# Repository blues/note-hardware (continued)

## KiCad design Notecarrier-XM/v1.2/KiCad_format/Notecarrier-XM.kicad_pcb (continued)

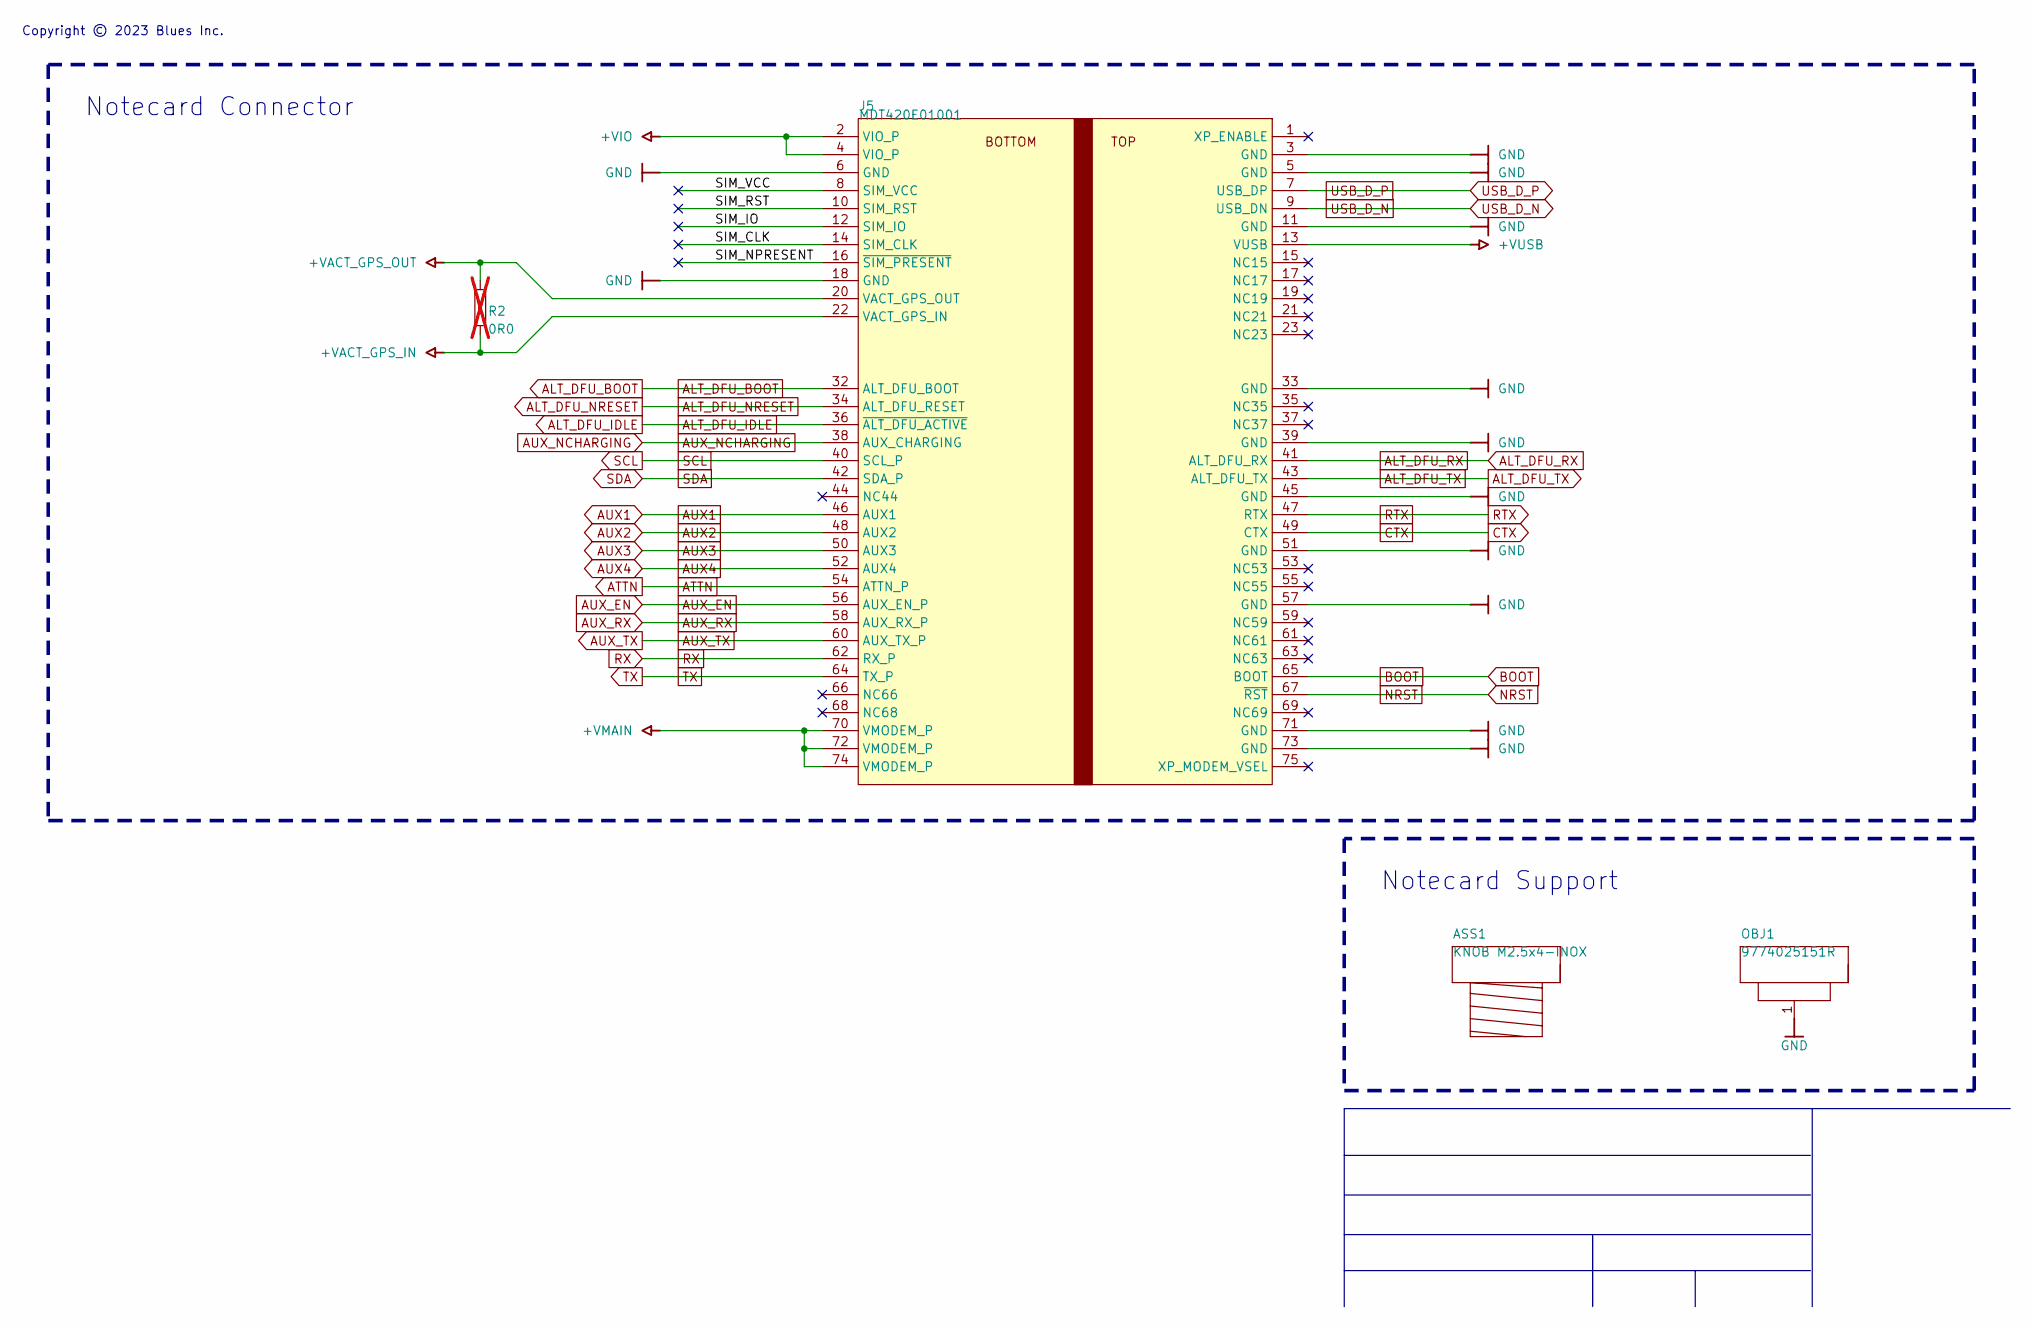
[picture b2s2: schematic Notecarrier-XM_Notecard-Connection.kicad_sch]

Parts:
ASS1: KNOB M2.5x4-INOX; MANUFACTURER PART NUMBER M2.5X4/D7985-A2
J5: MDT420E01001; J-75-0050-MOS-M2; MANUFACTURER PART NUMBER MDT420E03001
OBJ1: 9774025151R; DIST-WASMSIM0250; MANUFACTURER PART NUMBER 9774025151R
R2: 0R0; R-0603; MANUFACTURER PART NUMBER N/A; not fitted

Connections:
+VACT_GPS_IN: J5.22 (VACT_GPS_IN), R2.1; also elsewhere on the board
+VACT_GPS_OUT: J5.20 (VACT_GPS_OUT), R2.2; also elsewhere on the board
+VIO: J5.2 (VIO_P), J5.4 (VIO_P); also elsewhere on the board
+VMAIN: J5.70 (VMODEM_P), J5.72 (VMODEM_P), J5.74 (VMODEM_P); also elsewhere on the board
+VUSB: J5.13 (VUSB); also elsewhere on the board
/Notecard Connection/SIM_CLK: J5.14 (SIM_CLK)
/Notecard Connection/SIM_IO: J5.12 (SIM_IO)
/Notecard Connection/SIM_NPRESENT: J5.16 (~SIM_PRESENT)
/Notecard Connection/SIM_RST: J5.10 (SIM_RST)
/Notecard Connection/SIM_VCC: J5.8 (SIM_VCC)
ALT_DFU_BOOT: J5.32 (ALT_DFU_BOOT); also elsewhere on the board
ALT_DFU_IDLE: J5.36 (~ALT_DFU_ACTIVE); also elsewhere on the board
ALT_DFU_NRESET: J5.34 (ALT_DFU_RESET); also elsewhere on the board
ALT_DFU_RX: J5.41 (ALT_DFU_RX); also elsewhere on the board
ALT_DFU_TX: J5.43 (ALT_DFU_TX); also elsewhere on the board
ATTN: J5.54 (ATTN_P); also elsewhere on the board
AUX1: J5.46 (AUX1); also elsewhere on the board
AUX2: J5.48 (AUX2); also elsewhere on the board
AUX3: J5.50 (AUX3); also elsewhere on the board
AUX4: J5.52 (AUX4); also elsewhere on the board
AUX_EN: J5.56 (AUX_EN_P); also elsewhere on the board
AUX_NCHARGING: J5.38 (AUX_CHARGING); also elsewhere on the board
AUX_RX: J5.58 (AUX_RX_P); also elsewhere on the board
AUX_TX: J5.60 (AUX_TX_P); also elsewhere on the board
BOOT: J5.65 (BOOT); also elsewhere on the board
CTX: J5.49 (CTX); also elsewhere on the board
GND: J5.3 (GND), J5.5 (GND), J5.6 (GND), J5.11 (GND), J5.18 (GND), J5.33 (GND), J5.39 (GND), J5.45 (GND), J5.51 (GND), J5.57 (GND), J5.71 (GND), J5.73 (GND), OBJ1.1; also elsewhere on the board
NRST: J5.67 (~RST); also elsewhere on the board
RTX: J5.47 (RTX); also elsewhere on the board
RX: J5.62 (RX_P); also elsewhere on the board
SCL: J5.40 (SCL_P); also elsewhere on the board
SDA: J5.42 (SDA_P); also elsewhere on the board
TX: J5.64 (TX_P); also elsewhere on the board
USB_D_N: J5.9 (USB_DN); also elsewhere on the board
USB_D_P: J5.7 (USB_DP); also elsewhere on the board

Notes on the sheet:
Copyright © 2023 Blues Inc.
Notecard Connector
Notecard Support

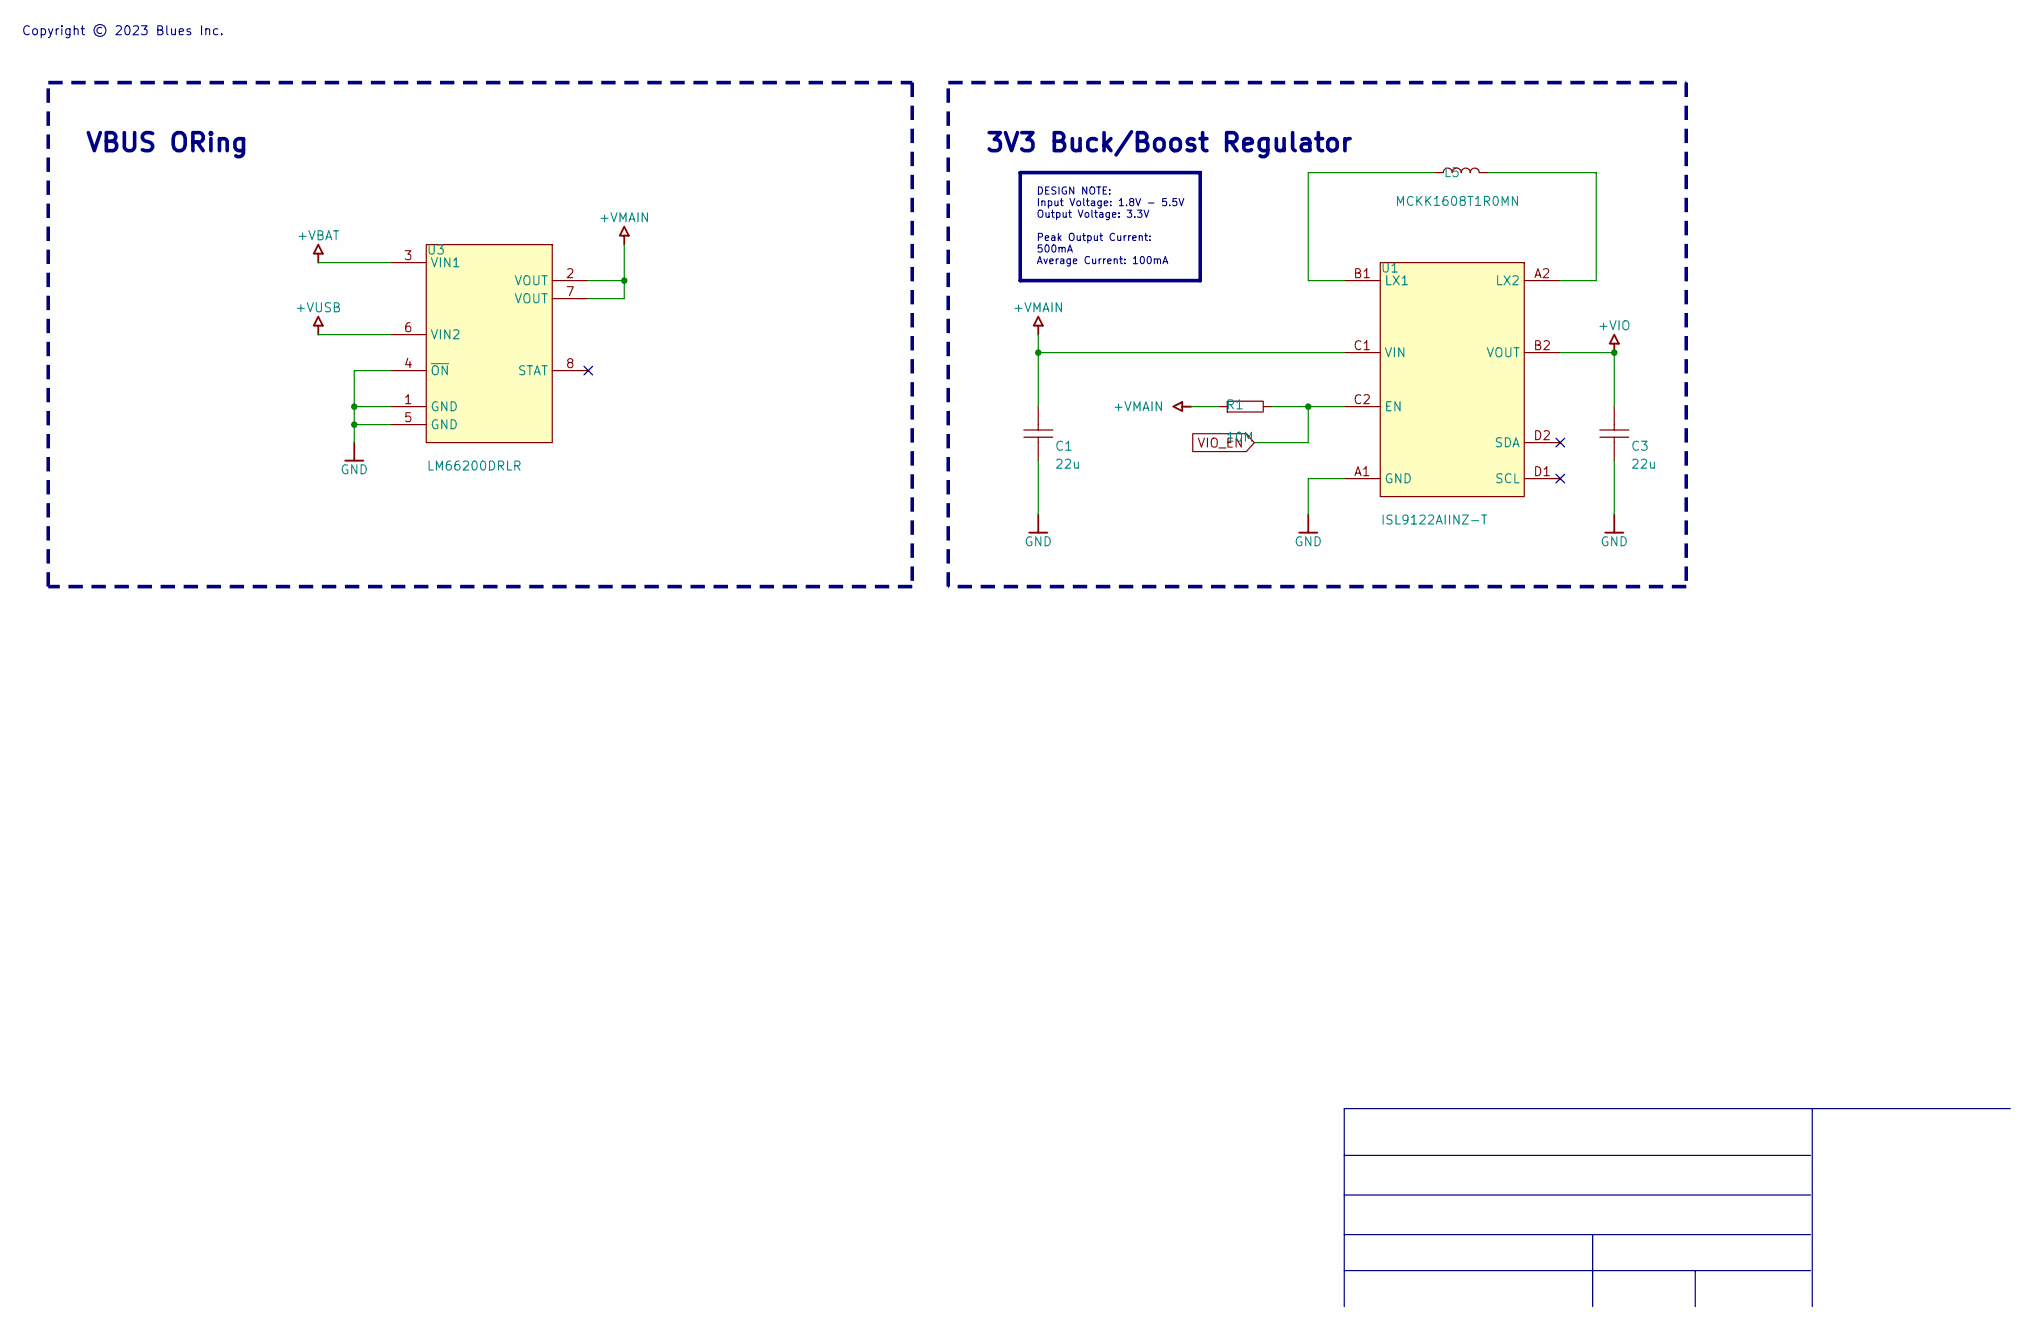
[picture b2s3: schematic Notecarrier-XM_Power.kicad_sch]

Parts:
C1, C3: 22u; C-0805; MANUFACTURER PART NUMBER N/A
L5: MCKK1608T1R0MN; L-0603; MANUFACTURER PART NUMBER MCKK1608T1R0MN
R1: 10M; R-0402; MANUFACTURER PART NUMBER N/A
U1: ISL9122AIINZ-T; BGA8N40P2X4_180x100x50; MANUFACTURER PART NUMBER ISL9122AIINZ-T
U3: LM66200DRLR; SOT-583; MANUFACTURER PART NUMBER LM66200DRLR

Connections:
+VBAT: U3.3 (VIN1); also elsewhere on the board
+VIO: C3.2, U1.B2 (VOUT); also elsewhere on the board
+VMAIN: C1.2, R1.1, U1.C1 (VIN), U3.2 (VOUT), U3.7 (VOUT); also elsewhere on the board
+VUSB: U3.6 (VIN2); also elsewhere on the board
GND: C1.1, C3.1, U1.A1 (GND), U3.1 (GND), U3.4 (~ON), U3.5 (GND); also elsewhere on the board
unnamed: L5.1, U1.B1 (LX1)
unnamed: L5.2, U1.A2 (LX2)
VIO_EN: R1.2, U1.C2 (EN); also elsewhere on the board

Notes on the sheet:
3V3 Buck/Boost Regulator
Copyright © 2023 Blues Inc.
VBUS ORing
DESIGN NOTE: Input Voltage: 1.8V - 5.5V Output Voltage: 3.3V Peak Output Current: 500mA Average Current: 100mA

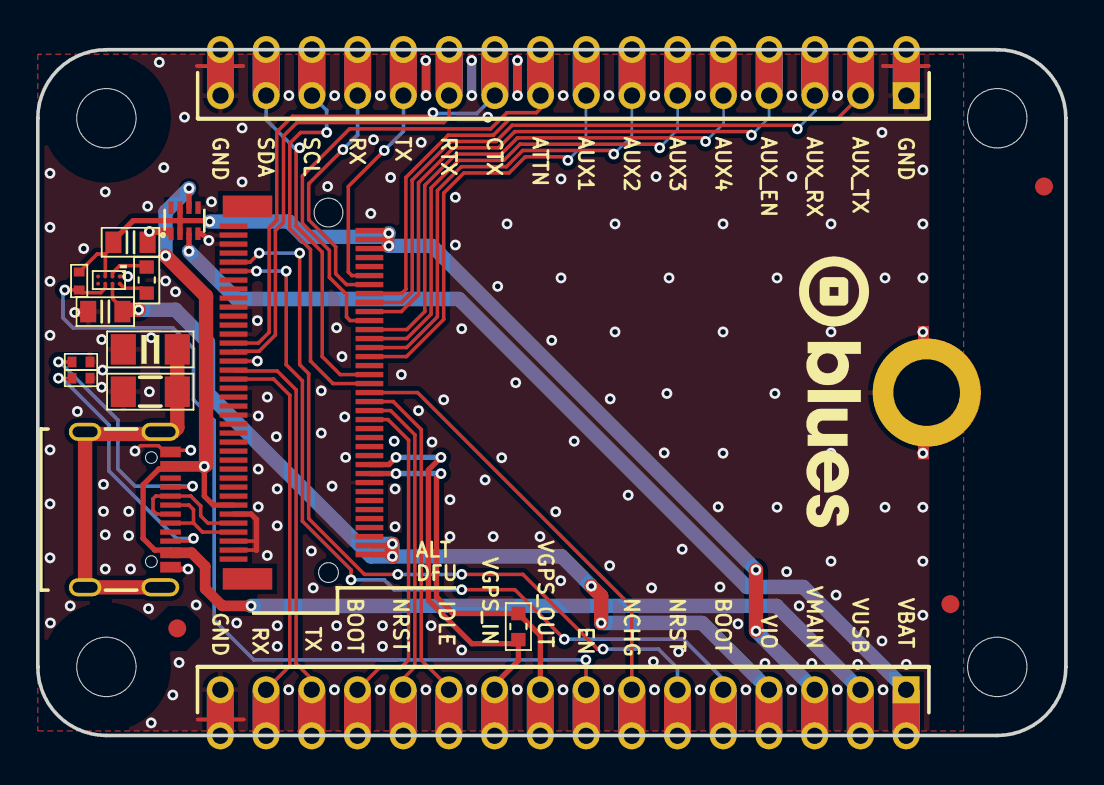
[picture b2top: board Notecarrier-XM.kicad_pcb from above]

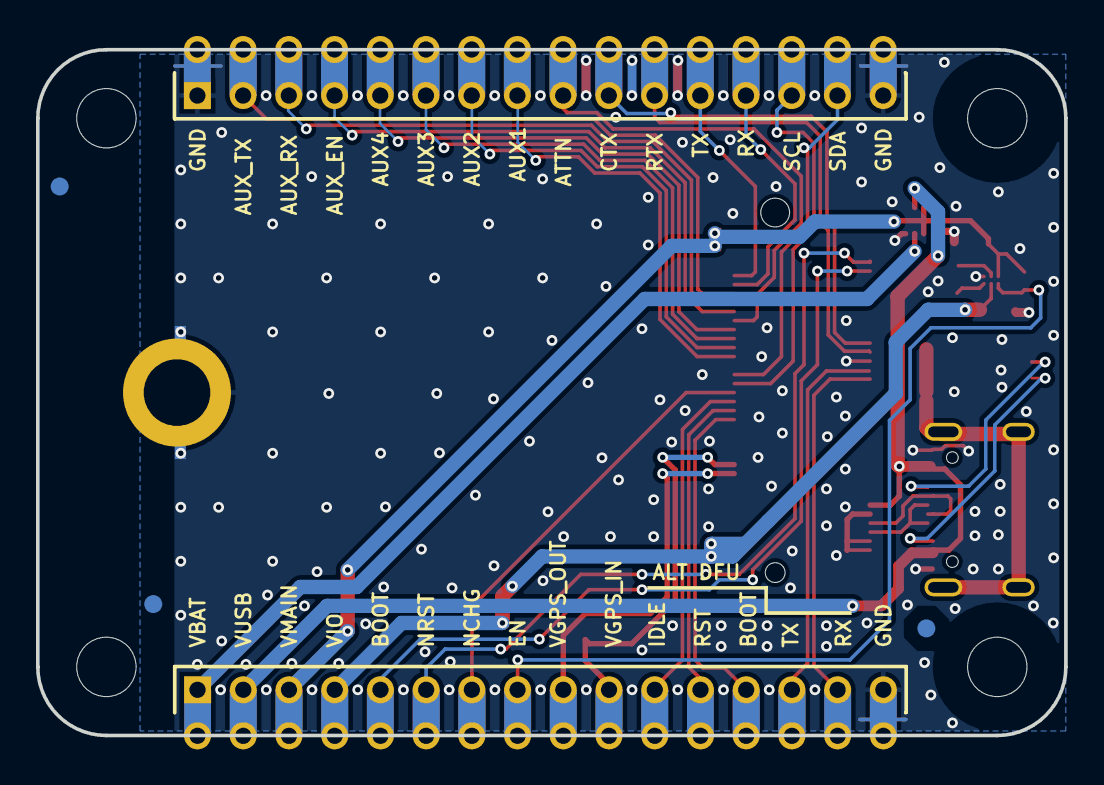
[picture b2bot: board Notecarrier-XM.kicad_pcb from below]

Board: 2 copper layers, 57.1 x 38.1 mm, 22 parts (3 on the bottom side), 37 nets.

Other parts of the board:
FD1, FD2, FD3, FD5, FD6, FD7: Fiducial mark; Fiducial mark 1mm

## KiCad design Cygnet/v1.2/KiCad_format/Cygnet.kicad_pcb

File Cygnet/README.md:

# Cygnet

STM32L433CC in Adafruit Feather form factor

  - Schematics
  - Bills of material
  - PCB layouts and Gerber files
  - Dimensioned drawings
  - KiCad design files ([v1.2/KiCad_format](v1.2/KiCad_format), converted from the original sources and validated against the shipped fabrication outputs)

> **⚠️ One open discrepancy in the KiCad port.** Inner layer 1 (`In1_Cu`) carries
> roughly fifty annular rings that the shipped Gerbers do not, so its fabrication
> equivalence on that layer is **not proven** and the gerber gate fails. Every
> other layer matches, and the schematic, netlist and BOM are exact. See
> [the porting notes](v1.2/KiCad_format/documentation/Porting-Notes.md) before
> using these files to manufacture.

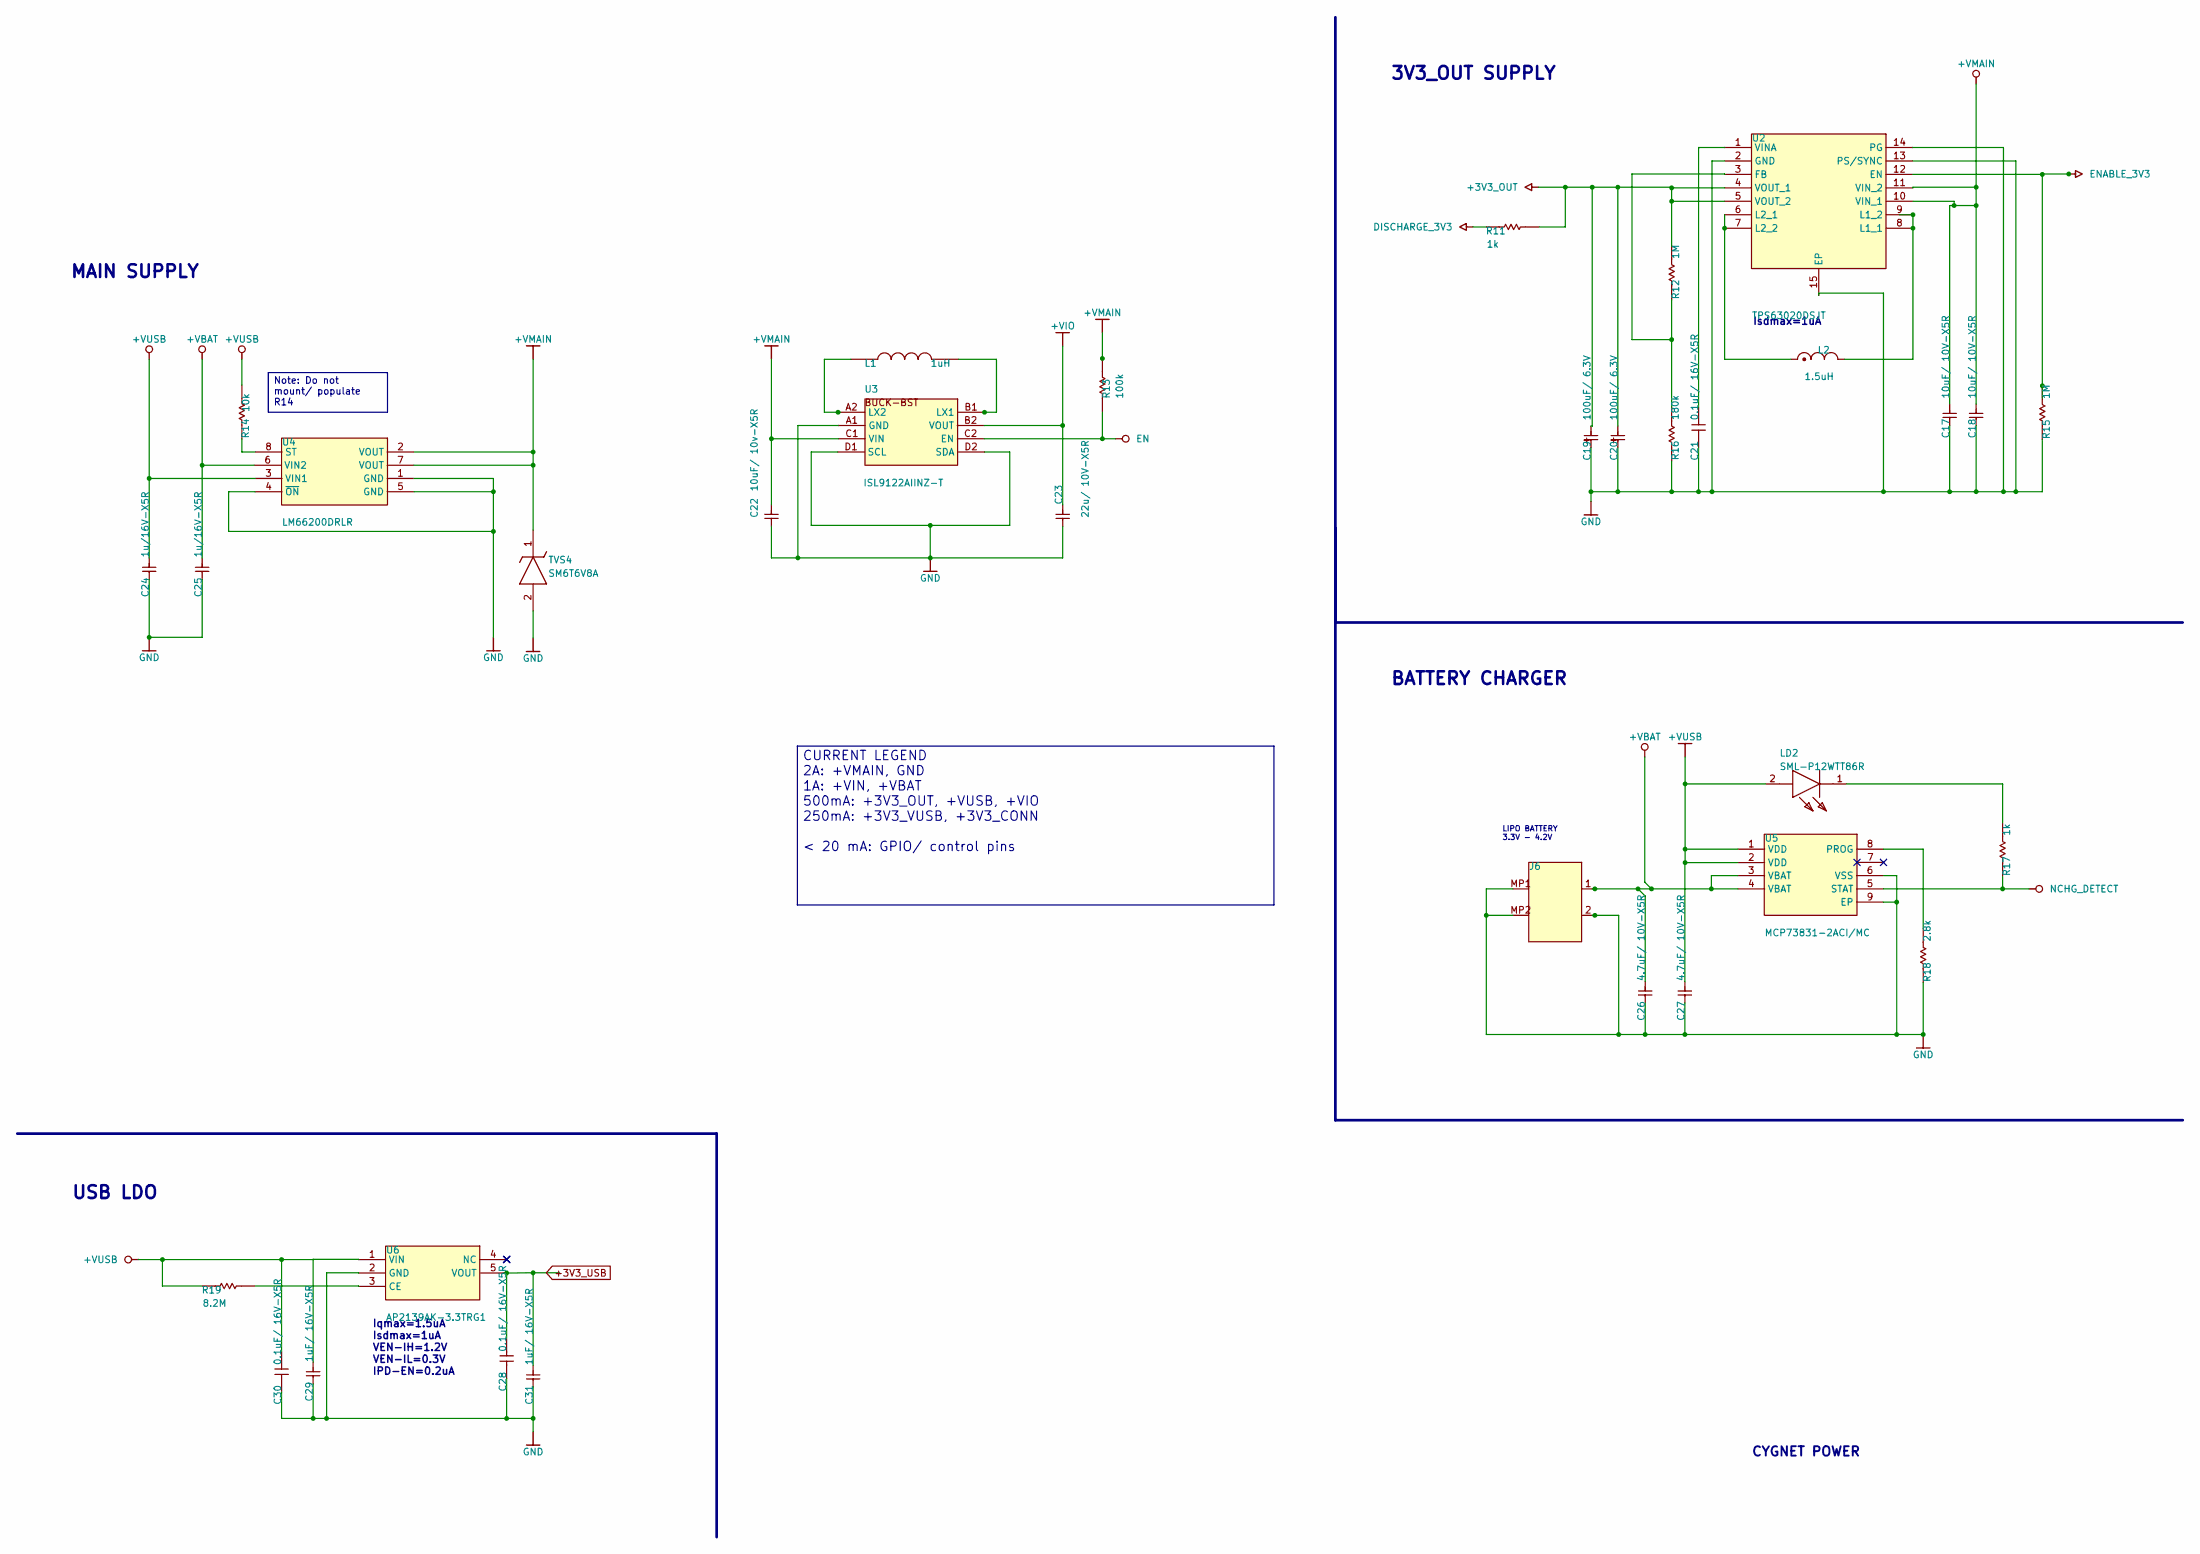
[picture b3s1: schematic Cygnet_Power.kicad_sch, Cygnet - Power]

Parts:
C17, C18: 10uF/ 10V-X5R; FP-GRM18-0_15-IPC_A; MPN GRM188R61A106KE69D
C19, C20: 100uF/ 6.3V; F930J107KAABE1-Footprint-1; MPN F930J107KAABE1
C21, C28, C30: 0.1uF/ 16V-X5R; GRM033R61C104KE84J-Footprint-1; MPN GRM033R61C104KE84J
C22: 10uF/ 10v-X5R; FP-GRM18-0_15-IPC_A; MPN GRM188R61A106KE69D
C23: 22u/ 10V-X5R; FP-GRM18-0_15-IPC_A; MPN GRM188R61A106KE69D
C24, C25: 1u/16V-X5R; C0402B105K016T-Footprint-1; MPN C0402B105K016T
C26, C27: 4.7uF/ 10V-X5R; FP-CL10-IPC_B; MPN CL10A475KP8NNNC
C29, C31: 1uF/ 16V-X5R; C0402B105K016T-Footprint-1; MPN C0402B105K016T
J6: 1769 - JST-PH 2-PIN SMT; 1769 - JST-PH 2-PIN SMT-Footprint-1
L1: 1uH; MCKK1608T1R0MN-Footprint-1; MPN MCKK1608T1R0MN
L2: 1.5uH; FP-XFL4020-MFG; MPN XFL4020-152MEC
LD2: SML-P12WTT86R; SML-P12WTT86R-Footprint-1; MPN SML-P12WTT86R
R11: 1k; RESC1005X40X25ML05T05; TOLERANCE 1%; MPN RC0402FR-071KL
R12, R15: 1M; RESC0201(0603)_M; MPN RC0201FR-071ML
R13: 100k; RESC0201(0603)_M
R14: 10k; RESC0603X26X15NL03T05; MPN MC0201L6F1002SE
R16: 180k; MR02X1803FAL-Footprint-1; MPN MR02X1803FAL
R17: 1k; RESC0603X28X15ML05T05; MPN CRCW02011K00FNED
R18: 2.8k; RESC0603X28X15ML05T05; MPN CRCW02012K80FKED
R19: 8.2M; CRCW02018M20FNED-Footprint-1; MPN CRCW02018M20FNED
TVS4: SM6T6V8A; SM6T6V8A-Footprint-1; MPN SM6T6V8A
U2: TPS63020DSJT; FP-DSJ0014A-MFG; MPN TPS63020DSJT
U3: ISL9122AIINZ-T; ISL9122AIINZ-T-Footprint-1; MPN ISL9122AIINZ-T
U4: LM66200DRLR; LM66200DRLR-Footprint-2; MPN LM66200DRLR
U5: MCP73831-2ACI/MC; FP-C04-123-IPC_A; MPN MCP73831-2ACI/MC
U6: AP2139AK-3.3TRG1; AP2139AK-3.3TRG1-Footprint-1

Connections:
+3V3_OUT: C19.1, C20.1, R11.2, R12.2, U2.4 (VOUT_1), U2.5 (VOUT_2); also elsewhere on the board
+3V3_USB: C28.1, C31.1, U6.5 (VOUT); also elsewhere on the board
+VBAT: C25.1, C26.1, J6.1, U4.6 (VIN2), U5.3 (VBAT), U5.4 (VBAT); also elsewhere on the board
+VIO: C23.1, U3.B2 (VOUT); also elsewhere on the board
+VMAIN: C17.1, C18.1, C22.1, R13.2, TVS4.1 (K), U2.10 (VIN_1), U2.11 (VIN_2), U3.C1 (VIN), U4.2 (VOUT), U4.7 (VOUT); also elsewhere on the board
+VUSB: C24.1, C27.1, C29.1, C30.1, LD2.2 (A), R14.2, R19.1, U4.3 (VIN1), U5.1 (VDD), U5.2 (VDD), U6.1 (VIN); also elsewhere on the board
DISCHARGE_3V3: R11.1; also elsewhere on the board
EN: R13.1, U3.C2 (EN); also elsewhere on the board
ENABLE_3V3: R15.2, U2.12 (EN); also elsewhere on the board
GND: C17.2, C18.2, C19.2, C20.2, C21.2, C22.2, C23.2, C24.2, C25.2, C26.2, C27.2, C28.2, C29.2, C30.2, C31.2, J6.2, J6.MP1, J6.MP2, R15.1, R16.1, R18.1, TVS4.2 (A), U2.2 (GND), U2.13 (PS/SYNC), U2.14 (PG), U2.15 (EP), U3.A1 (GND), U3.D1 (SCL), U3.D2 (SDA), U4.1 (GND), U4.4 (~ON), U4.5 (GND), U5.6 (VSS), U5.9 (EP), U6.2 (GND); also elsewhere on the board
NCHG_DETECT: R17.1, U5.5 (STAT); also elsewhere on the board
unnamed: LD2.1 (K), R17.2
unnamed: R12.1, R16.2, U2.3 (FB)
unnamed: L2.2, U2.8 (L1_1), U2.9 (L1_2)
unnamed: L2.1, U2.6 (L2_1), U2.7 (L2_2)
unnamed: C21.1, U2.1 (VINA)
unnamed: L1.2, U3.B1 (LX1)
unnamed: L1.1, U3.A2 (LX2)
unnamed: R14.1, U4.8 (ST)
unnamed: R18.2, U5.8 (PROG)
unnamed: R19.2, U6.3 (CE)

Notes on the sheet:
MAIN SUPPLY
CYGNET POWER
BATTERY CHARGER
Isdmax=1uA
3V3_OUT SUPPLY
USB LDO
Iqmax=1.5uA Isdmax=1uA VEN-IH=1.2V VEN-IL=0.3V IPD-EN=0.2uA
LIPO BATTERY 3.3V - 4.2V
Note: Do not mount/ populate R14
CURRENT LEGEND 2A: +VMAIN, GND 1A: +VIN, +VBAT 500mA: +3V3_OUT, +VUSB, +VIO 250mA: +3V3_VUSB, +3V3_CONN < 20 mA: GPIO/ control pins

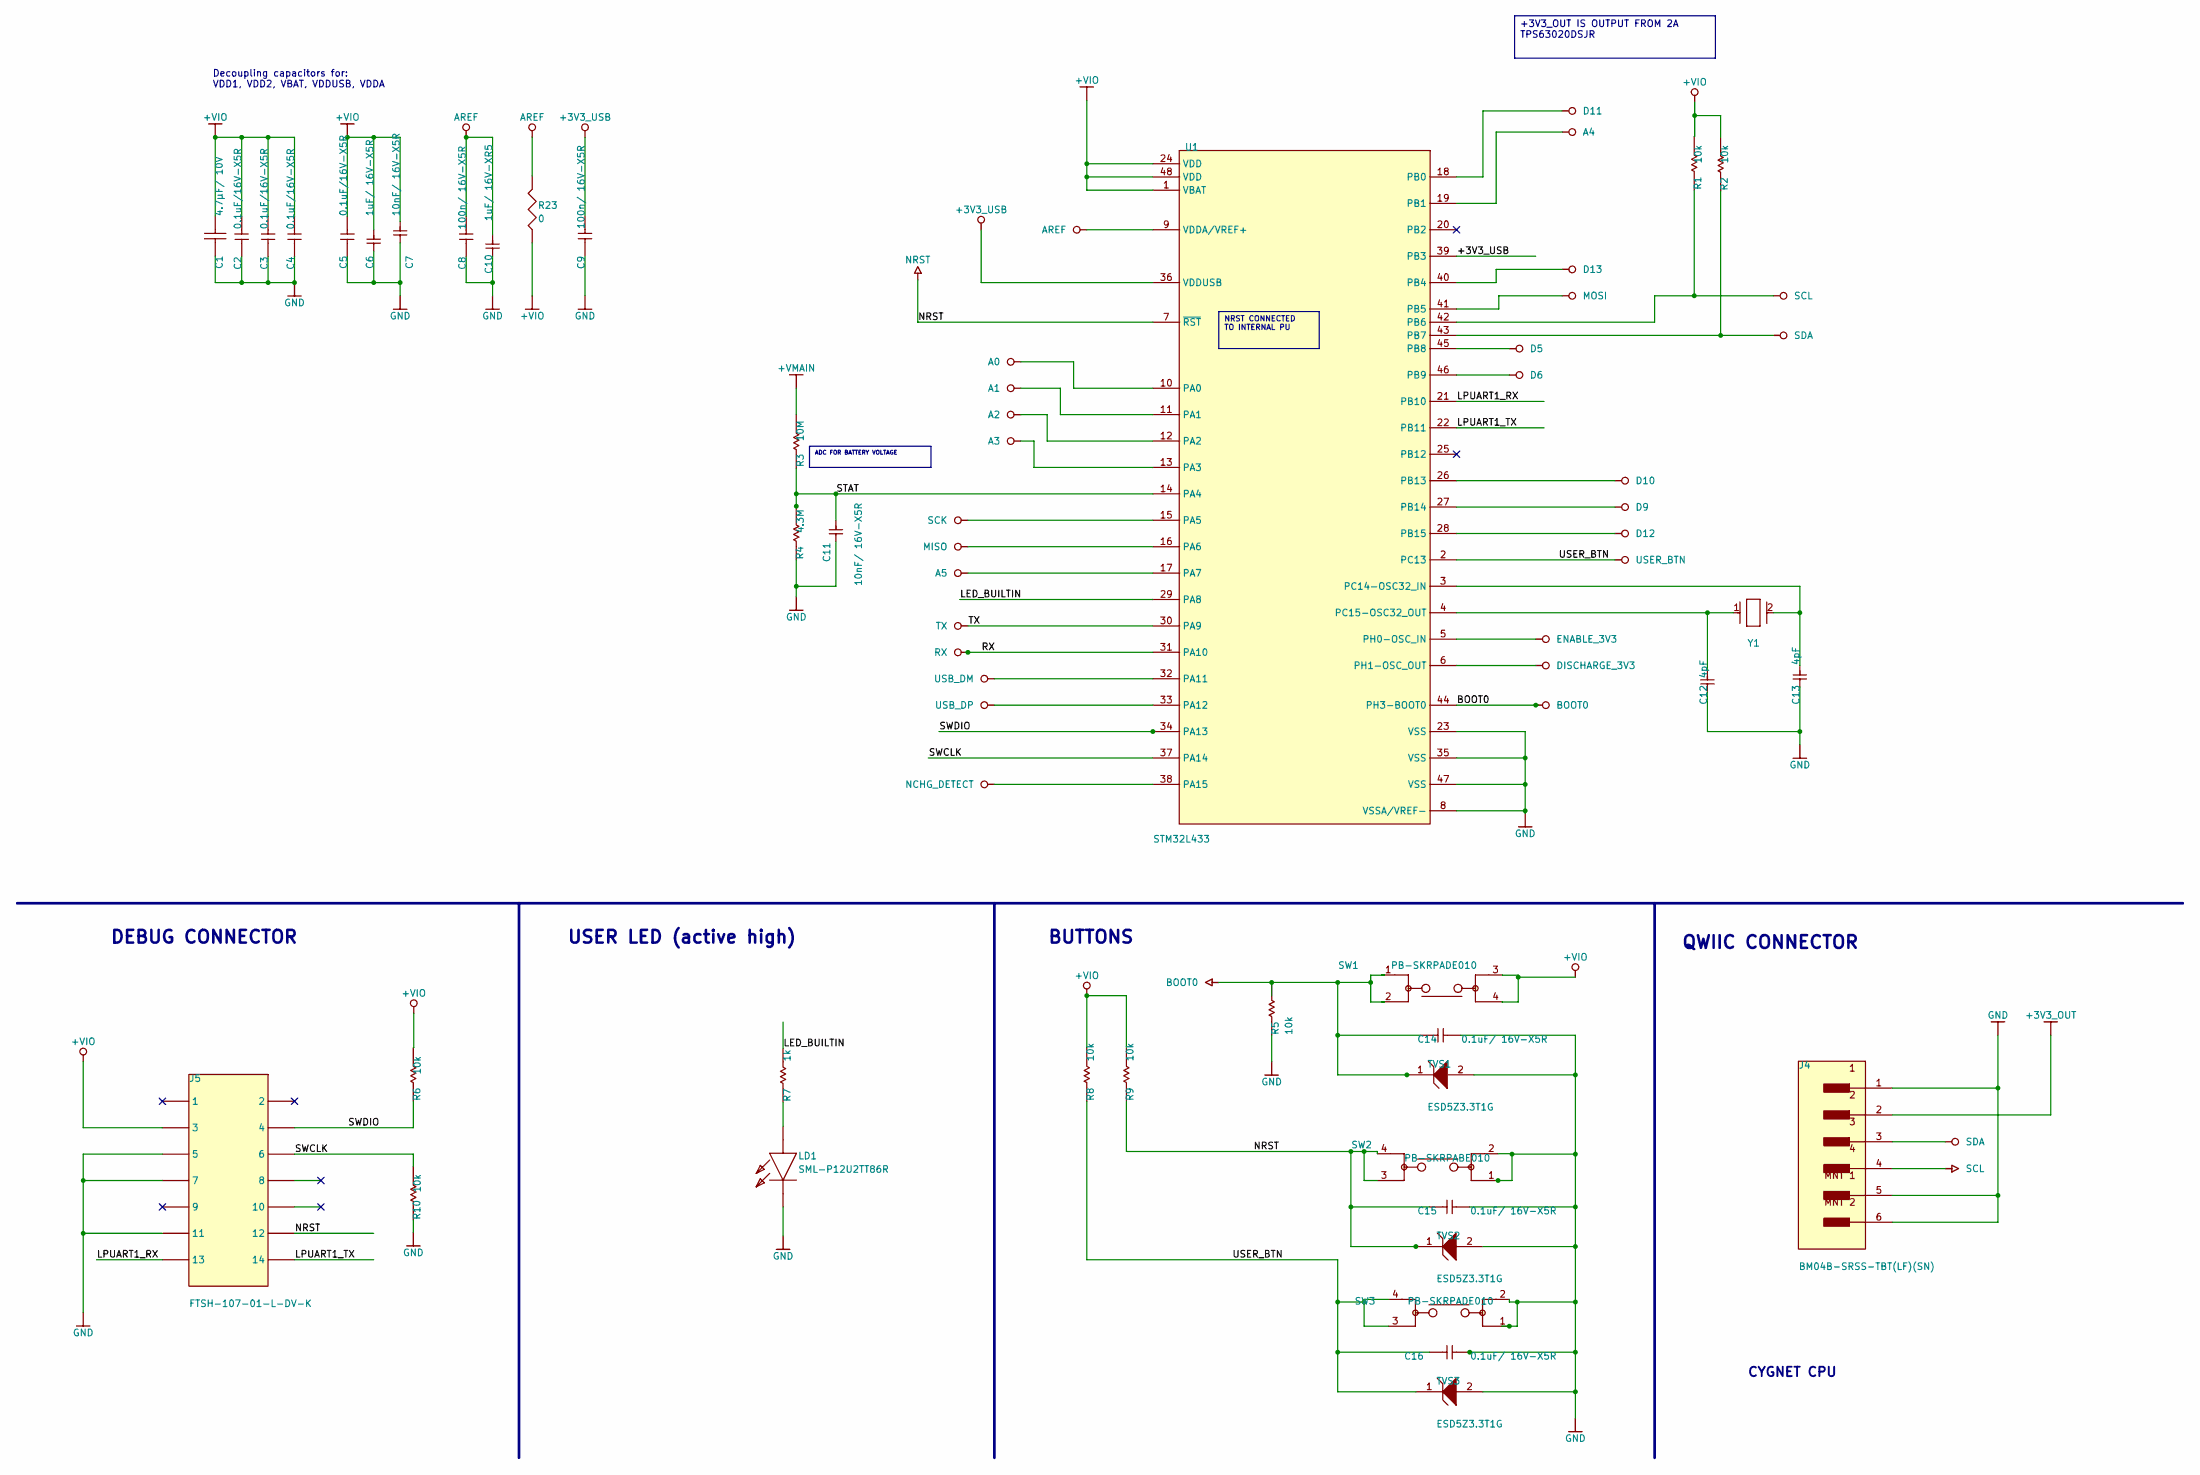
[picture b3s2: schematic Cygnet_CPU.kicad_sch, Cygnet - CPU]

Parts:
C1: 4.7µF/ 10V; CAPC0603(1608)100_L; TOLERANCE 10%; VOLTAGE RATING 10V; MPN C1608X5R1A475K/0.50
C2, C3, C4, C5: 0.1uF/16V-X5R; GRM033R61C104KE84J-Footprint-1; MPN GRM033R61C104KE84J
C6: 1uF/ 16V-X5R; C0402B105K016T-Footprint-1; MPN C0402B105K016T
C7, C11: 10nF/ 16V-X5R; FP-GRM033-0_03-MFG; MPN GRM033R61C103KA12D
C8, C9: 100n/ 16V-X5R; GRM033R61C104KE84J-Footprint-1; MPN GRM033R61C104KE84J
C10: 1uF/ 16V-XR5; C0402B105K016T-Footprint-1; MPN C0402B105K016T
C12, C13: 4pF; FP-GRM033-0_03-MFG; MPN GRM0335C1H4R0BA01D
C14, C15, C16: 0.1uF/ 16V-X5R; GRM033R61C104KE84J-Footprint-1; MPN GRM033R61C104KE84J
J4: BM04B-SRSS-TBT(LF)(SN); FP-BM04B-SRSS-TBT_LF_SN-MFG; MPN BM04B-SRSS-TBT(LF)(SN)
J5: FTSH-107-01-L-DV-K; FP-FTSH-107-01-L-DV-K-MFG; MPN FTSH-107-01-L-DV-K
LD1: SML-P12U2TT86R; SML-P12U2TT86R-Footprint-1; MPN SML-P12U2TT86R
R1, R2, R5, R6, R8, R9, R10: 10k; RESC0603X26X15NL03T05; MPN MC0201L6F1002SE
R3: 10M; RESC0603X26X15NL03T05; MPN RK73H1HTTC1005F
R4: 4.3M; RESC0603X26X15NL03T05; MPN RK73H1HTTC4304F
R7: 1k; RESC0603X28X15ML05T05; MPN CRCW02011K00FNED
R23: Jumper 0603; RESC0603(1608)_L
SW1, SW3: PB-SKRPADE010; CAPC1005X06N; MPN SKRPADE010
SW2: PB-SKRPABE010; CAPC1005X06N; MPN SKRPABE010
TVS1, TVS2, TVS3: ESD5Z3.3T1G; ONSC-SOD-523-2-502-01_V; MPN ESD5Z3.3T1G
U1: STM32L433; FP-LQFP48-5B-IPC_A; MPN STM32L433CB
Y1: ABS06-107-32.768KHZ-T; FP-ABS06-MFG; MPN ABS06-107-32.768KHZ-T

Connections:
+3V3_OUT: J4.2; also elsewhere on the board
+3V3_USB: C9.1, U1.36 (VDDUSB), U1.39 (PB3); also elsewhere on the board
+VIO: C1.2, C2.1, C3.1, C4.1, C5.1, C6.1, C7.1, J5.3, R1.2, R2.2, R6.2, R8.2, R9.2, R23.1, SW1.3, SW1.4, U1.1 (VBAT), U1.24 (VDD), U1.48 (VDD); also elsewhere on the board
+VMAIN: R3.2; also elsewhere on the board
/CPU/LED_BUILTIN: R7.2, U1.29 (PA8)
/CPU/LPUART1_RX: J5.13, U1.21 (PB10)
/CPU/LPUART1_TX: J5.14, U1.22 (PB11)
/CPU/STAT: C11.1, R3.1, R4.2, U1.14 (PA4)
/CPU/SWCLK: J5.6, R10.2, U1.37 (PA14)
/CPU/SWDIO: J5.4, R6.1, U1.34 (PA13)
A0: U1.10 (PA0); also elsewhere on the board
A1: U1.11 (PA1); also elsewhere on the board
A2: U1.12 (PA2); also elsewhere on the board
A3: U1.13 (PA3); also elsewhere on the board
A4: U1.19 (PB1); also elsewhere on the board
A5: U1.17 (PA7); also elsewhere on the board
AREF: C8.1, C10.1, R23.2, U1.9 (VDDA/VREF+); also elsewhere on the board
BOOT0: C14.1, R5.2, SW1.1, SW1.2, TVS1.1 (K), U1.44 (PH3-BOOT0); also elsewhere on the board
D5: U1.45 (PB8); also elsewhere on the board
D6: U1.46 (PB9); also elsewhere on the board
D9: U1.27 (PB14); also elsewhere on the board
D10: U1.26 (PB13); also elsewhere on the board
D11: U1.18 (PB0); also elsewhere on the board
D12: U1.28 (PB15); also elsewhere on the board
D13: U1.40 (PB4); also elsewhere on the board
DISCHARGE_3V3: U1.6 (PH1-OSC_OUT); also elsewhere on the board
ENABLE_3V3: U1.5 (PH0-OSC_IN); also elsewhere on the board
GND: C1.1, C2.2, C3.2, C4.2, C5.2, C6.2, C7.2, C8.2, C9.2, C10.2, C11.2, C12.2, C13.2, C14.2, C15.2, C16.2, J4.1, J4.5 (MNT_1), J4.6 (MNT_2), J5.5, J5.7, J5.11, LD1.1 (K), R4.1, R5.1, R10.1, SW2.1, SW2.2, SW3.1, SW3.2, TVS1.2 (A), TVS2.2 (A), TVS3.2 (A), U1.8 (VSSA/VREF-), U1.23 (VSS), U1.35 (VSS), U1.47 (VSS); also elsewhere on the board
MISO: U1.16 (PA6); also elsewhere on the board
MOSI: U1.41 (PB5); also elsewhere on the board
NCHG_DETECT: U1.38 (PA15); also elsewhere on the board
NRST: C15.1, J5.12, R9.1, SW2.3, SW2.4, TVS2.1 (K), U1.7 (~RST); also elsewhere on the board
unnamed: LD1.2 (A), R7.1
unnamed: C13.1, U1.3 (PC14-OSC32_IN), Y1.2
unnamed: C12.1, U1.4 (PC15-OSC32_OUT), Y1.1
RX: U1.31 (PA10); also elsewhere on the board
SCK: U1.15 (PA5); also elsewhere on the board
SCL: J4.4, R1.1, U1.42 (PB6); also elsewhere on the board
SDA: J4.3, R2.1, U1.43 (PB7); also elsewhere on the board
TX: U1.30 (PA9); also elsewhere on the board
USB_DM: U1.32 (PA11); also elsewhere on the board
USB_DP: U1.33 (PA12); also elsewhere on the board
USER_BTN: C16.1, R8.1, SW3.3, SW3.4, TVS3.1 (K), U1.2 (PC13)

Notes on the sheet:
USER LED (active high)
QWIIC CONNECTOR
BUTTONS
CYGNET CPU
DEBUG CONNECTOR
ADC FOR BATTERY VOLTAGE
Decoupling capacitors for: VDD1, VDD2, VBAT, VDDUSB, VDDA
+3V3_OUT IS OUTPUT FROM 2A TPS63020DSJR
NRST CONNECTED TO INTERNAL PU
